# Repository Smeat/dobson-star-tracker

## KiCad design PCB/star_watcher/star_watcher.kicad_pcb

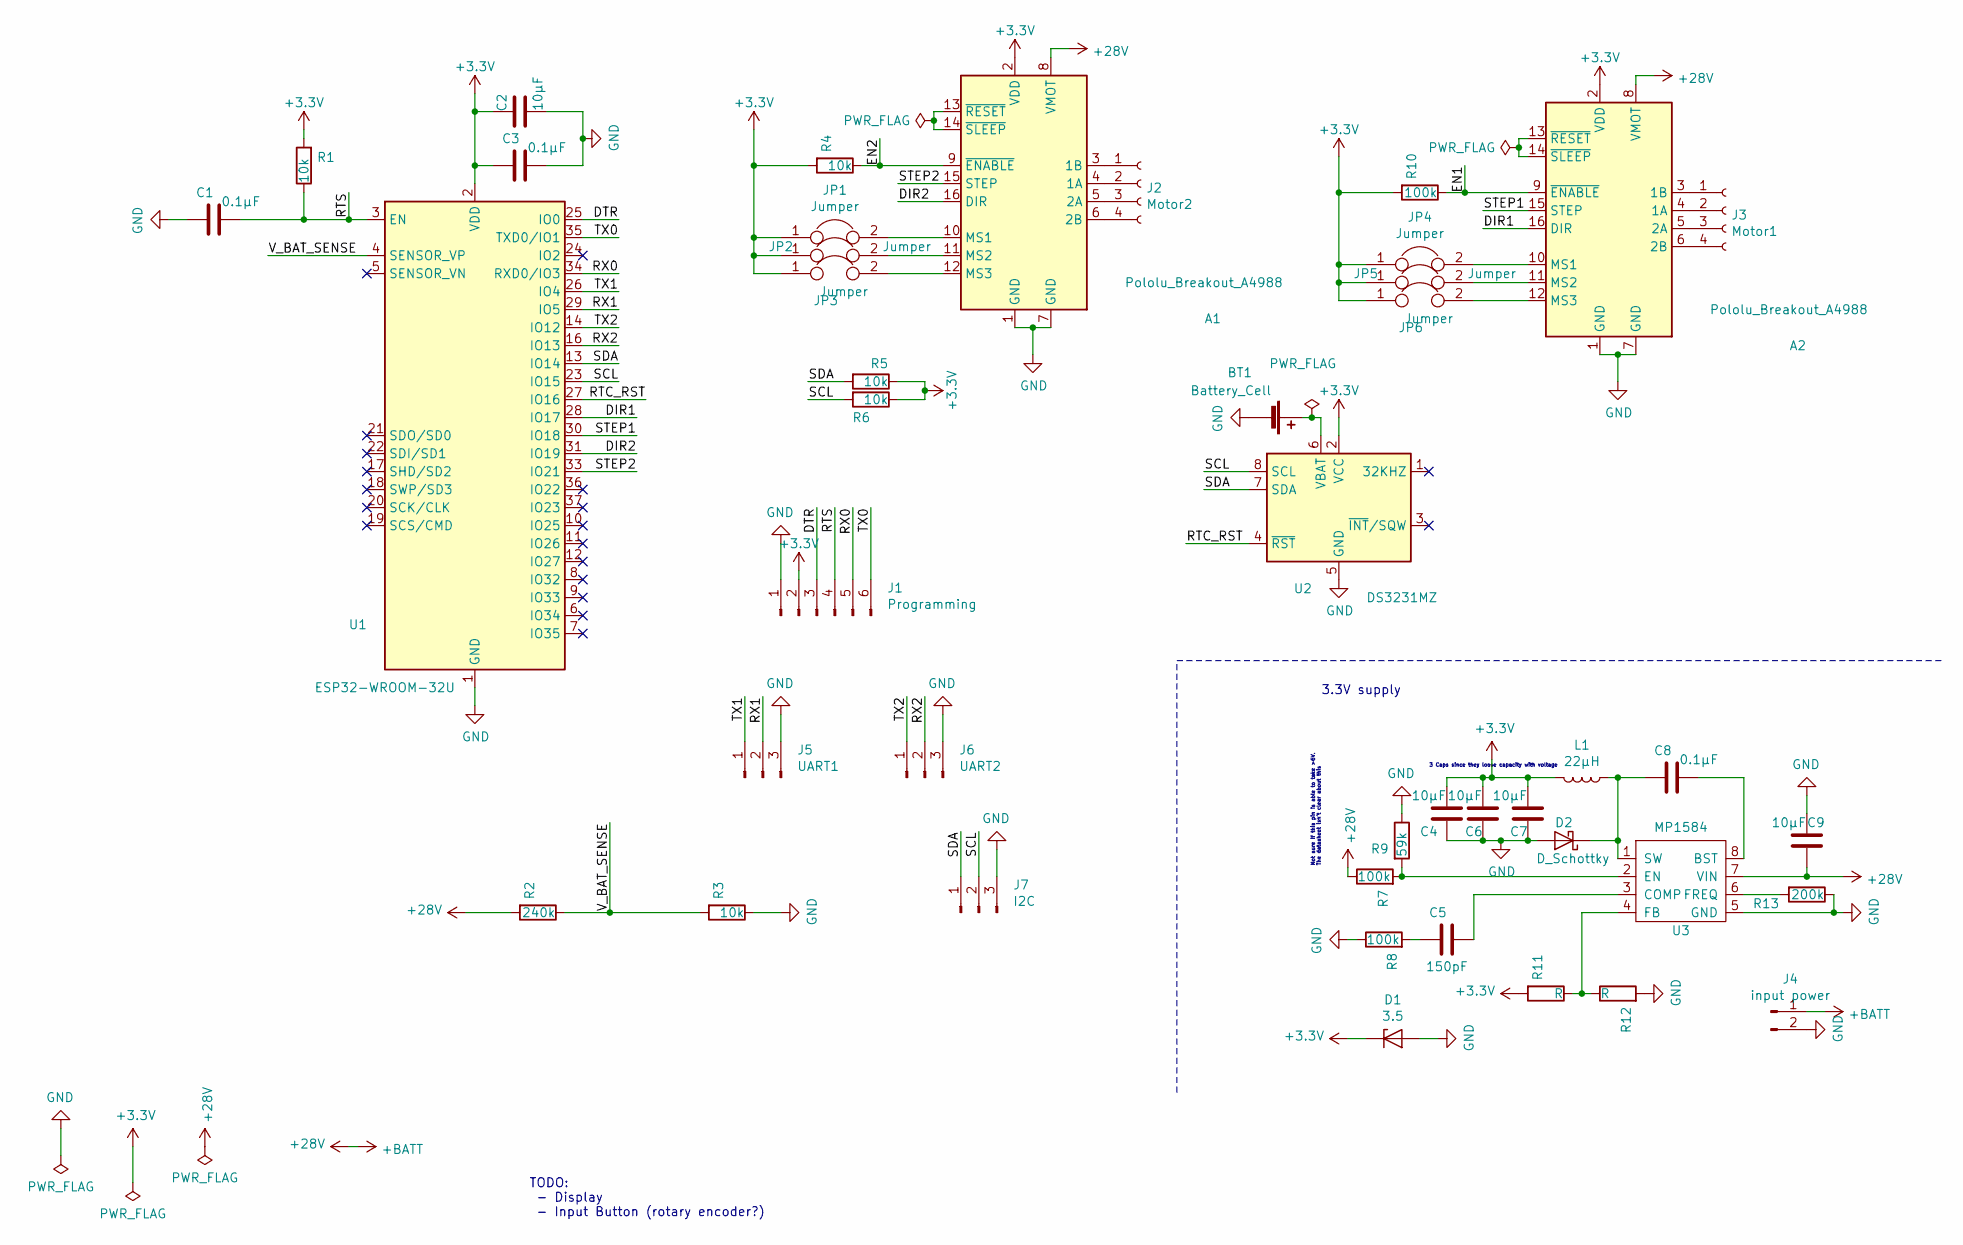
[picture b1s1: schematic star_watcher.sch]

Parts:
A1, A2: Pololu_Breakout_A4988; Pololu_Breakout-16_15.2x20.3mm
BT1: Battery_Cell; BatteryHolder_Keystone_103_1x20mm
C1, C3, C8: 0.1µF; C_0603_1608Metric
C2, C4, C6, C7, C9: 10µF; C_0805_2012Metric
C5: 150pF; C_0603_1608Metric
D1: 3.5; D_MELF
D2: D_Schottky; D_SMA
J1: Programming; PinHeader_1x06_P2.54mm_Vertical
J2: Motor2; PinHeader_1x04_P2.54mm_Vertical
J3: Motor1; PinHeader_1x04_P2.54mm_Vertical
J4: input power; SolderWirePad_1x02_P7.62mm_Drill2.5mm
J5: UART1; PinHeader_1x03_P2.54mm_Vertical
J6: UART2; PinHeader_1x03_P2.54mm_Vertical
J7: I2C; PinHeader_1x03_P2.54mm_Vertical
JP1, JP2, JP3, JP4, JP5, JP6: Jumper; PinHeader_1x02_P2.54mm_Vertical
L1: 22µH; L_12x12mm_H6mm
R1, R3, R4, R5, R6: 10k; R_0805_2012Metric
R2: 240k; R_0805_2012Metric
R7, R8, R10: 100k; R_0805_2012Metric
R9: 59k; R_0805_2012Metric
R11, R12: R; R_0805_2012Metric
R13: 200k; R_0805_2012Metric
U1: ESP32-WROOM-32U; ESP32-WROOM-32
U2: DS3231MZ; SOIC-8_3.9x4.9mm_P1.27mm
U3: MP1584; SOIC-8_3.9x4.9mm_P1.27mm

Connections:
+3V3: A1.2 (VDD), A2.2 (VDD), C2.1, C3.2, C4.2, C6.2, C7.2, D1.1 (K), J1.2, JP1.1, JP2.1, JP3.1, JP4.1, JP5.1, JP6.1, L1.2, R1.2, R4.2, R5.1, R6.1, R10.2, R11.2, U1.2 (VDD), U2.2 (VCC)
+28V: A1.8 (VMOT), A2.8 (VMOT), C9.1, J4.1, R2.2, R7.1, U3.7 (VIN)
/DIR1: A2.16 (DIR), U1.28 (IO17)
/DIR2: A1.16 (DIR), U1.31 (IO19)
/DTR: J1.3, U1.25 (IO0)
/EN1: A2.9 (~ENABLE), R10.1
/EN2: A1.9 (~ENABLE), R4.1
/RTC_RST: U1.27 (IO16), U2.4 (~RST)
/RTS: C1.1, J1.4, R1.1, U1.3 (EN)
/RX0: J1.5, U1.34 (RXD0/IO3)
/RX1: J5.2, U1.29 (IO5)
/RX2: J6.2, U1.16 (IO13)
/SCL: J7.2, R6.2, U1.23 (IO15), U2.8 (SCL)
/SDA: J7.1, R5.2, U1.13 (IO14), U2.7 (SDA)
/STEP1: A2.15 (STEP), U1.30 (IO18)
/STEP2: A1.15 (STEP), U1.33 (IO21)
/TX0: J1.6, U1.35 (TXD0/IO1)
/TX1: J5.1, U1.26 (IO4)
/TX2: J6.1, U1.14 (IO12)
/V_BAT_SENSE: R2.1, R3.2, U1.4 (SENSOR_VP)
GND: A1.1 (GND), A1.7 (GND), A2.1 (GND), A2.7 (GND), BT1.2 (-), C1.2, C2.2, C3.1, C4.1, C6.1, C7.1, C9.2, D1.2 (A), D2.2 (A), J1.1, J4.2, J5.3, J6.3, J7.3, R3.1, R8.1, R9.1, R12.2, R13.1, U1.1 (GND), U1.15 (GND), U1.38 (GND), U1.39 (GND), U2.5 (GND), U3.5 (GND)
unnamed: A1.3 (1B), J2.1
unnamed: A1.4 (1A), J2.2
unnamed: A1.5 (2A), J2.3
unnamed: A1.6 (2B), J2.4
unnamed: A1.10 (MS1), JP1.2
unnamed: A1.11 (MS2), JP2.2
unnamed: A1.12 (MS3), JP3.2
unnamed: A1.13 (~RESET), A1.14 (~SLEEP)
unnamed: A2.3 (1B), J3.1
unnamed: A2.4 (1A), J3.2
unnamed: A2.5 (2A), J3.3
unnamed: A2.6 (2B), J3.4
unnamed: A2.10 (MS1), JP4.2
unnamed: A2.11 (MS2), JP5.2
unnamed: A2.12 (MS3), JP6.2
unnamed: A2.13 (~RESET), A2.14 (~SLEEP)
unnamed: BT1.1 (+), U2.6 (VBAT)
unnamed: C5.1, U3.3 (COMP)
unnamed: C5.2, R8.2
unnamed: C8.1, U3.8 (BST)
unnamed: C8.2, D2.1 (K), L1.1, U3.1 (SW)
unnamed: R7.2, R9.2, U3.2 (EN)
unnamed: R11.1, R12.1, U3.4 (FB)
unnamed: R13.2, U3.6 (FREQ)

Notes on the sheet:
Not sure if this pin is able to take >6V. The datasheet isn't clear about this
3 Caps since they loose capacity with voltage
3.3V supply
TODO: - Display - Input Button (rotary encoder?)

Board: 2 copper layers, 44 parts (4 on the bottom side), 45 nets, no tracks yet.

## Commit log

2020-04-01 Add platformio and esp32 support Totatlly untested and awful, but compiles ;)
2020-04-01 Change license to gpl3 for now
2020-04-01 Fix gitignore Thats why you always need a newline at the end ;)
2020-04-01 Add first draft for a pcb
2020-04-02 PCB should be feature complete now Just a few capacitors and startup IO stuff missing.
2020-04-02 Add vfat benchmark
2020-04-03 Add tool for creating star image
2020-04-03 Use nokia 5110 as display
2020-04-03 Fix sector alignment
2020-04-03 Add support for getting data from simbad
2020-04-03 Fix type header alignment and add types
2020-04-03 Change endianess
